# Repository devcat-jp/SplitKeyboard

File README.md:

# SplitKeyboard
勉強用に作成している分割キーボードです

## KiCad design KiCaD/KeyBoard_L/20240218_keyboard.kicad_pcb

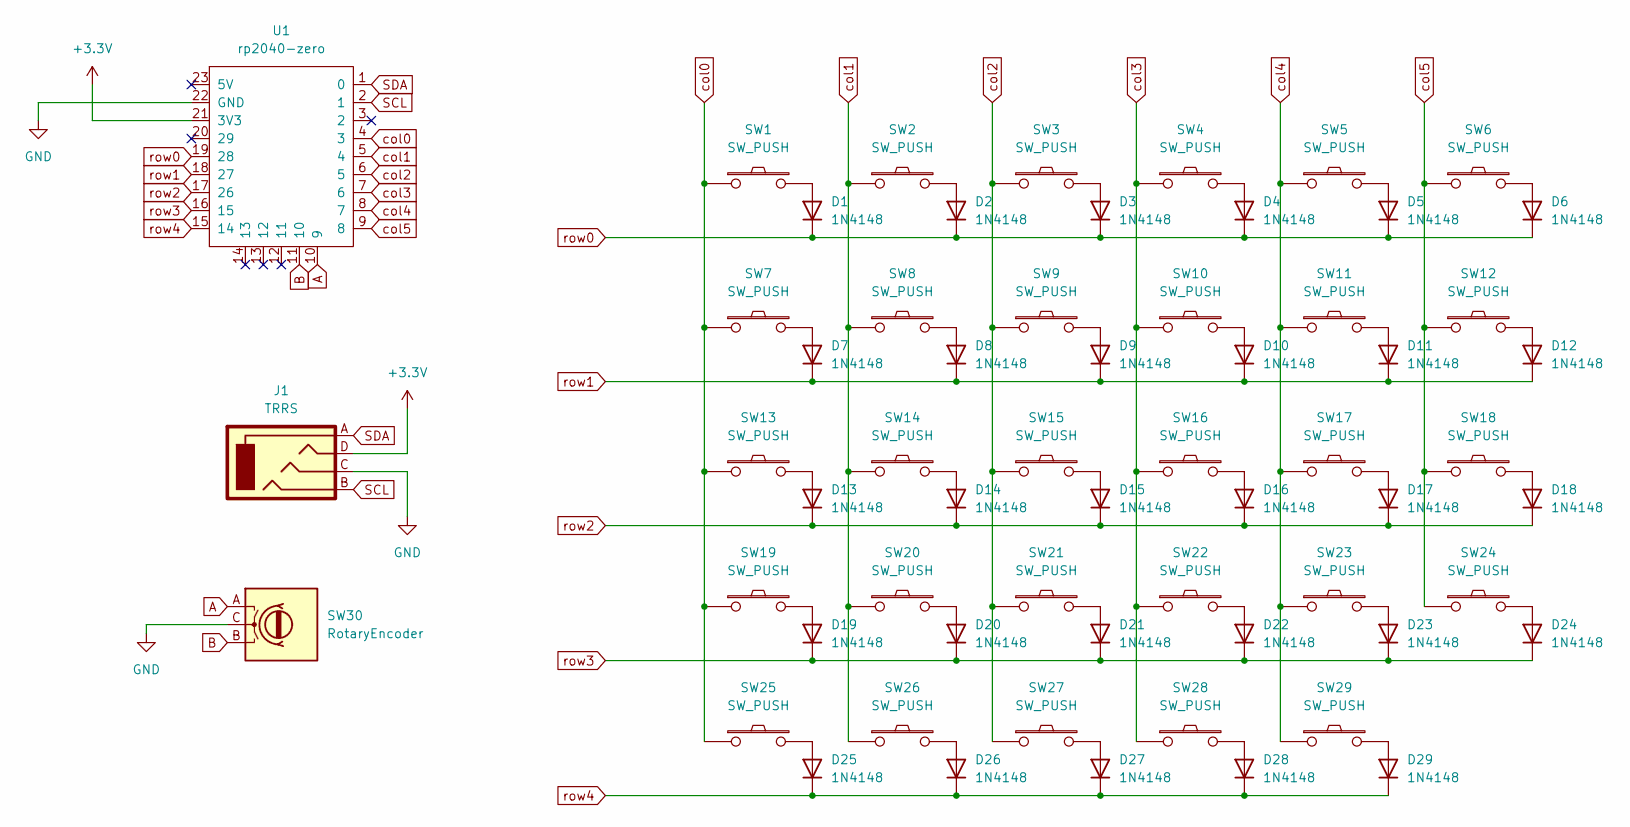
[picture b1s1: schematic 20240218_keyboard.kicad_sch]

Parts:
D1, D2, D3, D4, D5, D6, D7, D8, D9, D10, D11, D12, D13, D14, D15, D16, D17, D18, D19, D20, D21, D22, D23, D24, D25, D26, D27, D28, D29: 1N4148; D3_SMD_v2
J1: TRRS; MJ-4PP-9_1side
SW1, SW2, SW3, SW4, SW5, SW6, SW8, SW9, SW10, SW11, SW12, SW14, SW15, SW16, SW17, SW18, SW20, SW21, SW22, SW23, SW24, SW26, SW27, SW28: SW_PUSH; SW_Hotswap_Kailh_MX_1.00u
SW7: SW_PUSH; SW_Hotswap_Kailh_MX_1.25u
SW13, SW25, SW29: SW_PUSH; SW_Hotswap_Kailh_MX_1.50u
SW19: SW_PUSH; SW_Hotswap_Kailh_MX_1.75u
SW30: RotaryEncoder; RotaryEncoder_EC11-Switch
U1: rp2040-zero; rp2040-zero-tht

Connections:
+3.3V: J1.D, U1.21 (3V3)
A: SW30.A, U1.10 (9)
B: SW30.B, U1.11 (10)
GND: J1.C, SW30.C, U1.22 (GND)
unnamed: D1.2 (A), SW1.2
unnamed: D2.2 (A), SW2.2
unnamed: D3.2 (A), SW3.2
unnamed: D4.2 (A), SW4.2
unnamed: D5.2 (A), SW5.2
unnamed: D6.2 (A), SW6.2
unnamed: D7.2 (A), SW7.2
unnamed: D8.2 (A), SW8.2
unnamed: D9.2 (A), SW9.2
unnamed: D10.2 (A), SW10.2
unnamed: D11.2 (A), SW11.2
unnamed: D12.2 (A), SW12.2
unnamed: D13.2 (A), SW13.2
unnamed: D14.2 (A), SW14.2
unnamed: D15.2 (A), SW15.2
unnamed: D16.2 (A), SW16.2
unnamed: D17.2 (A), SW17.2
unnamed: D18.2 (A), SW18.2
unnamed: D19.2 (A), SW19.2
unnamed: D20.2 (A), SW20.2
unnamed: D21.2 (A), SW21.2
unnamed: D22.2 (A), SW22.2
unnamed: D23.2 (A), SW23.2
unnamed: D24.2 (A), SW24.2
unnamed: D25.2 (A), SW25.2
unnamed: D26.2 (A), SW26.2
unnamed: D27.2 (A), SW27.2
unnamed: D28.2 (A), SW28.2
unnamed: D29.2 (A), SW29.2
SCL: J1.B, U1.2 (1)
SDA: J1.A, U1.1 (0)
col0: SW1.1, SW7.1, SW13.1, SW19.1, SW25.1, U1.4 (3)
col1: SW2.1, SW8.1, SW14.1, SW20.1, SW26.1, U1.5 (4)
col2: SW3.1, SW9.1, SW15.1, SW21.1, SW27.1, U1.6 (5)
col3: SW4.1, SW10.1, SW16.1, SW22.1, SW28.1, U1.7 (6)
col4: SW5.1, SW11.1, SW17.1, SW23.1, SW29.1, U1.8 (7)
col5: SW6.1, SW12.1, SW18.1, SW24.1, U1.9 (8)
row0: D1.1 (K), D2.1 (K), D3.1 (K), D4.1 (K), D5.1 (K), D6.1 (K), U1.19 (28)
row1: D7.1 (K), D8.1 (K), D9.1 (K), D10.1 (K), D11.1 (K), D12.1 (K), U1.18 (27)
row2: D13.1 (K), D14.1 (K), D15.1 (K), D16.1 (K), D17.1 (K), D18.1 (K), U1.17 (26)
row3: D19.1 (K), D20.1 (K), D21.1 (K), D22.1 (K), D23.1 (K), D24.1 (K), U1.16 (15)
row4: D25.1 (K), D26.1 (K), D27.1 (K), D28.1 (K), D29.1 (K), U1.15 (14)

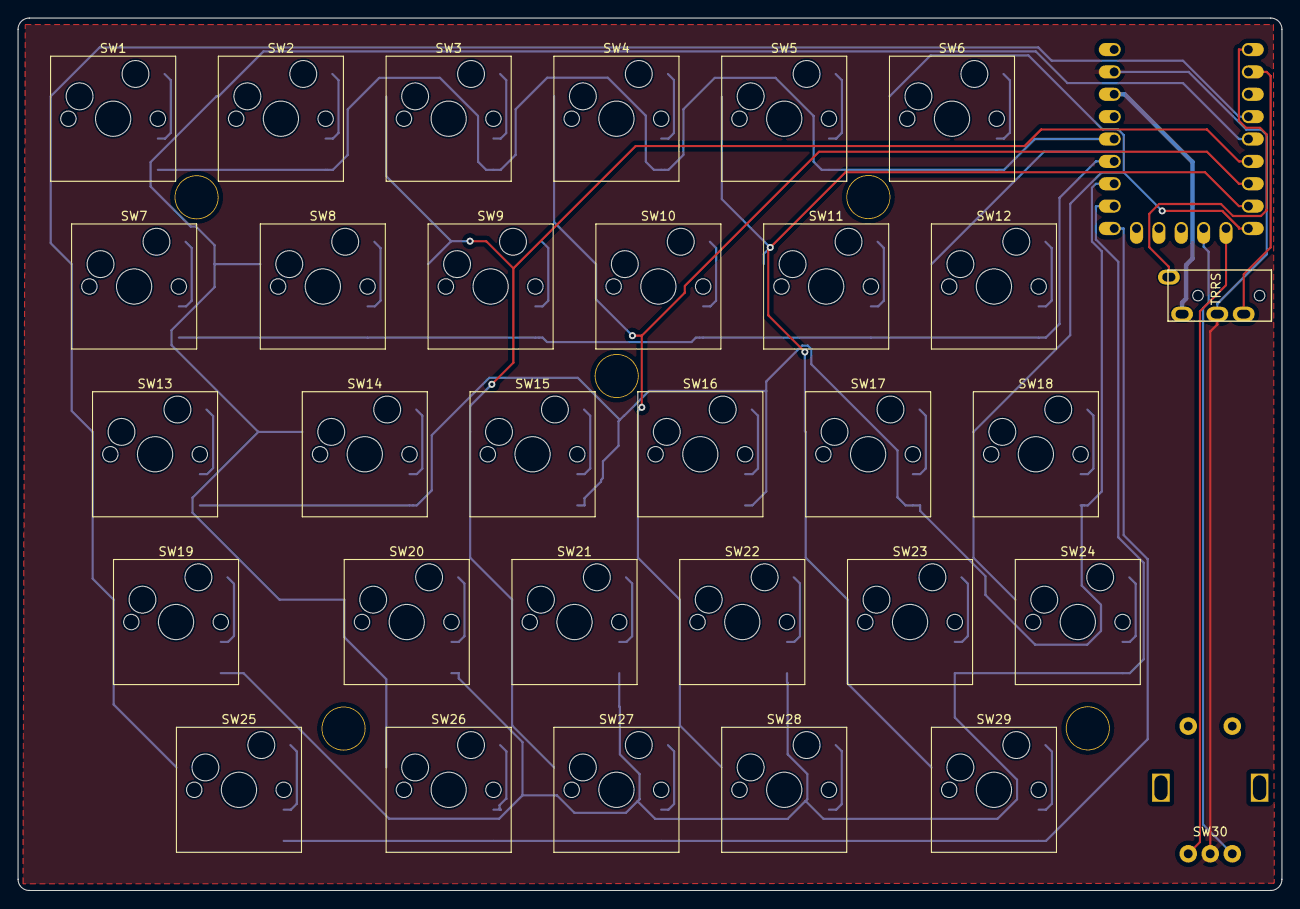
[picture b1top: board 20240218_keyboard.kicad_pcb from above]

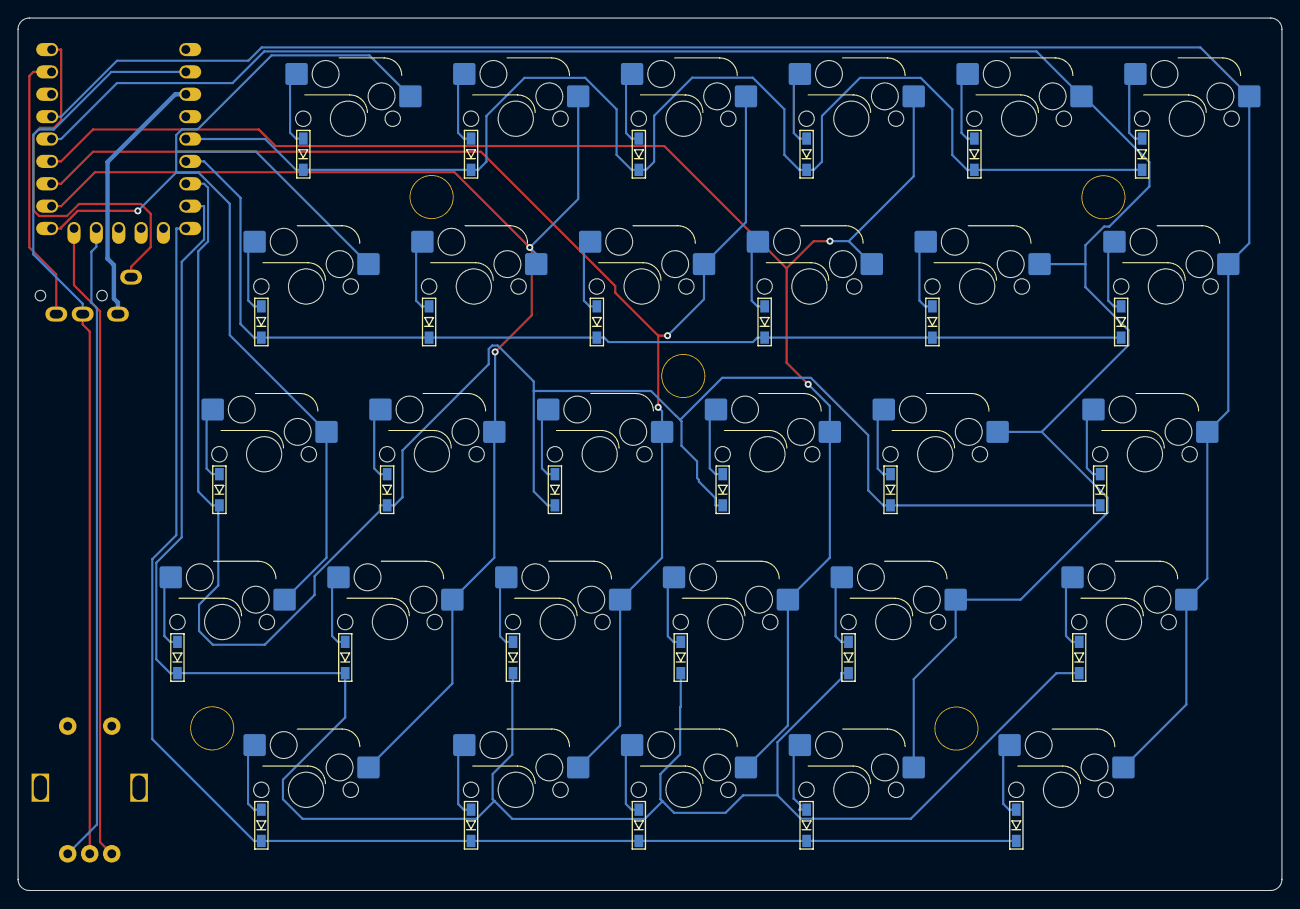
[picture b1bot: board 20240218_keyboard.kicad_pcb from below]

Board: 2 copper layers, 143.5 x 99.1 mm, 66 parts (29 on the bottom side), 46 nets.

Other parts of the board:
Ref01, Ref02, Ref03, Ref04, Ref05: Val**; HOLE

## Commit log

2024-03-23 [add] 成果物登録
2024-03-24 [mod] スレーブ側の入力情報をビットで送信
2024-03-24 [mod] マルチスレッド化と通信確認用のバイト追加
2024-03-31 [mod] マウス機能試作
2024-04-03 [mod] キーアサイン変更
2024-04-09 [mod ] LED点灯を削除
2024-04-09 [mod] マウス系の機能を削除
2024-04-10 [mod] キー入力処理を見直し
2024-04-16 [mod] キー押しっぱなしの処理修正、およびWindwosキーの押しっぱなし処理追加
2024-04-16 [mod] 裏レイヤにバックスペースを追加
2024-04-16 [mod] 特殊キーは両方のレイヤで同じキーとする
2024-04-16 [mod] 裏レイヤーにFキーを設定
